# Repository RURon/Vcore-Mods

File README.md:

# Vcore-Mods #

My mods for my Ratrig VCore3-300 build

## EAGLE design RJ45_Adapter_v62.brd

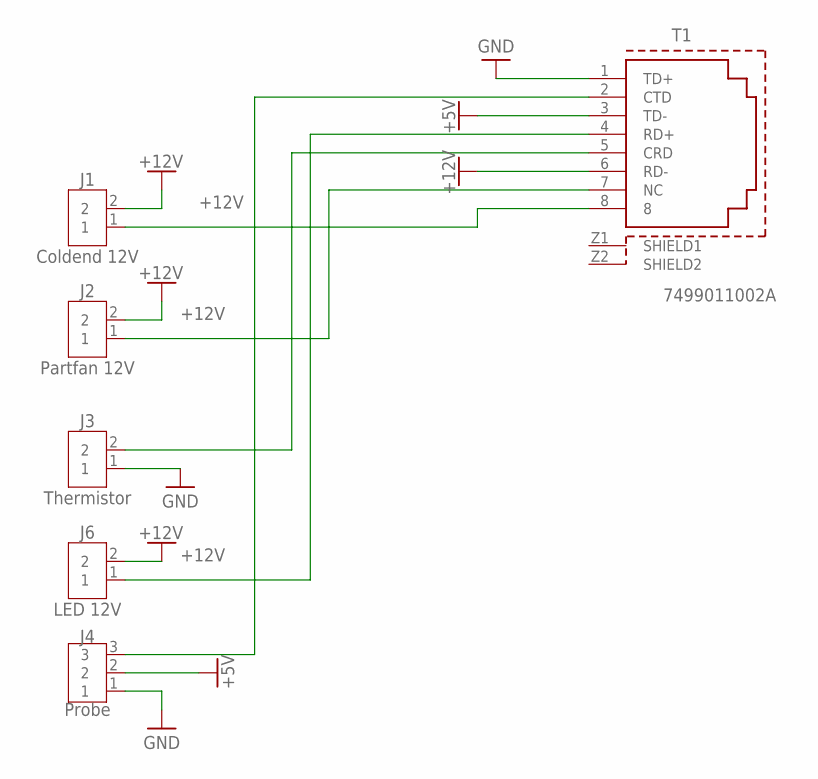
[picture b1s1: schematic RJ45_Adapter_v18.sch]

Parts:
J1: Coldend 12V; B2B-XH-A
J2: Partfan 12V; B2B-XH-A
J3: Thermistor; B2B-XH-A
J4: Probe; B3B-XH-A
J6: LED 12V; B2B-XH-A
T1: 7499011002A

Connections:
+5V: J4.2, T1.3 (TD-)
+12V: J1.2, J2.2, J6.2, T1.6 (RD-)
GND: J3.1, J4.1, T1.1 (TD+)
unnamed: J4.3, T1.2 (CTD)
unnamed: J3.2, T1.5 (CRD)
unnamed: J6.1, T1.4 (RD+)
unnamed: J2.1, T1.7 (NC)
unnamed: J1.1, T1.8

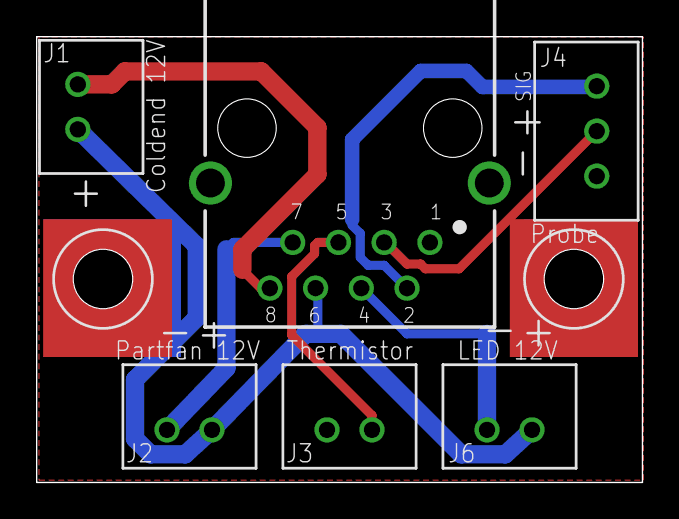
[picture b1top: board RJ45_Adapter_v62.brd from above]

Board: 2 copper layers, 33.7 x 24.8 mm, 6 parts (0 on the bottom side), 8 nets.

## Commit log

2021-08-06 Create test
2021-08-06 moving files
2021-08-06 Rename RJ45_Adapter_v62.brd to RJ45 Breakout/RJ45_Adapter_v62.brd
2021-08-06 Update and rename test to readme
2021-08-06 Rename readme to readme.txt
2021-08-06 Rename readme.txt to README.md
2021-08-07 Rename README to README.md
2021-08-07 Add files via upload
    removed a cable clip and raised LEDs by 1mm further up
2021-08-08 again little update
2021-08-08 Update README.md
    Changed to 4,5mm LED strip
2021-08-08 New cable clip
2021-08-08 New part
2021-10-26 STLs
2021-10-26 STEPs added
2021-10-30 new photo
2021-10-30 First publish
2021-11-01 new mod
2021-11-01 revise
2021-11-01 renamed
2021-11-01 release
2021-11-17 Update Bottom Corner RearLeft.step
    Moved cable outlet further to the corner and added cable guide
2021-11-17 Added STLs
2021-11-23 updated design
2021-12-21 Update
    Added handle and matching new fron bottom bar. Small improvements on various bottom parts to result in more consistent profiles
2022-02-15 Update README.md
    STL files not up to date!
2022-07-25 New bed arms

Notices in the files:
parts and their libraries:
Wurth_Signal: Copyright: Würth Elektronik
